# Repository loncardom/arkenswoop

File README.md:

# Arkenswoop

A WIP fork of [jimmerricks's Swoop](https://github.com/jimmerricks/swoop), which is a fork of [David Barr's Sweep](https://github.com/davidphilipbarr/Sweep), which is itself based on the fabulous [Ferris by Pierre Chevalier](https://github.com/pierrechevalier83/ferris).

| Front | Back |
| :---: | :---: |
|  |  |

### Features

⭕ Low profile Kailh Choc switches  
⭕ Hotswap  
⭕ Dual side-scrolling encoder  
⭕ Oled screens  
⭕ Power switch for battery management  
⭕ Bluetooth support w/ nice!nano  
⭕ Plate style case with mcu cover

### Components list

To build and use an Arkenswoop you will need:

* 1× PCB Kit (1.6mm thickness when ordering)
* 1× back plate kit (optional, 1.2mm thickness when ordering)
* 2× promicro compatible boards or 2 nice!nanos.
* 34× Kailh Choc v1 switches
* 34× Kailh Choc hotswap sockets (PG1350)
* 34× keycaps
* 34× SMD diodes (1N4148W, SOD-123)
* 2× side-scrolling encoders EVQWGD001
* 2× OLED LCD Display 128x32 SSD1306 (optional)
* 2× MCU cover (optional, 1mm thickness when ordering)
* 2× reset switches (optional; B3U-1000P(M))
* Some little rubber feet/bumpers (minimum of 4 on each side)
* 2× power switches (wireless only; MSK 12C02)
* 2× lipo batteries (wireless only; 301230 or 301228)
* 1× TRRS (not TRS!) cable (wired only)
* 2× TRRS Jack [PJ-320A] (wired only)
* 1× USB Cable (depends on your micro-controller choice)

## Images

<details>
    <summary>Assembled Arkenswoop 0.6.0</summary>
    
</details>
<details>
    <summary>Back of assembled Arkenswoop 0.6.0</summary>
    
</details>

# Altenswoop

An Arkenswoop inspired keyboard with a twist: the Z and / keys are moved to the side.

| Front | Back |
| :---: | :---: |
|  |  |

### Features

⭕ Low profile Kailh Choc switches  
⭕ Hotswap  
⭕ Dual side-scrolling encoder  
⭕ Oled screens  
⭕ Power switch for battery management  
⭕ Bluetooth support w/ nice!nano  
⭕ Plate style case with mcu cover

### Components list

To build and use an Altenswoop you will need:

* 1× PCB Kit (1.6mm thickness when ordering)
* 1× back plate kit (optional, 1.2mm thickness when ordering)
* 2× promicro compatible boards or 2 nice!nanos.
* 34× Kailh Choc v1 switches
* 34× Kailh Choc hotswap sockets (PG1350)
* 34× keycaps
* 34× SMD diodes (1N4148W, SOD-123)
* 2× side-scrolling encoders EVQWGD001
* 2× OLED LCD Display 128x32 SSD1306 (optional)
* 2× MCU cover (optional, 1mm thickness when ordering)
* 2× reset switches (optional; B3U-1000P(M))
* Some little rubber feet/bumpers (minimum of 4 on each side)
* 2× power switches (wireless only; MSK 12C02)
* 2× lipo batteries (wireless only; 301230 or 301228)
* 1× TRRS (not TRS!) cable (wired only)
* 2× TRRS Jack [PJ-320A] (wired only)
* 1× USB Cable (depends on your micro-controller choice)

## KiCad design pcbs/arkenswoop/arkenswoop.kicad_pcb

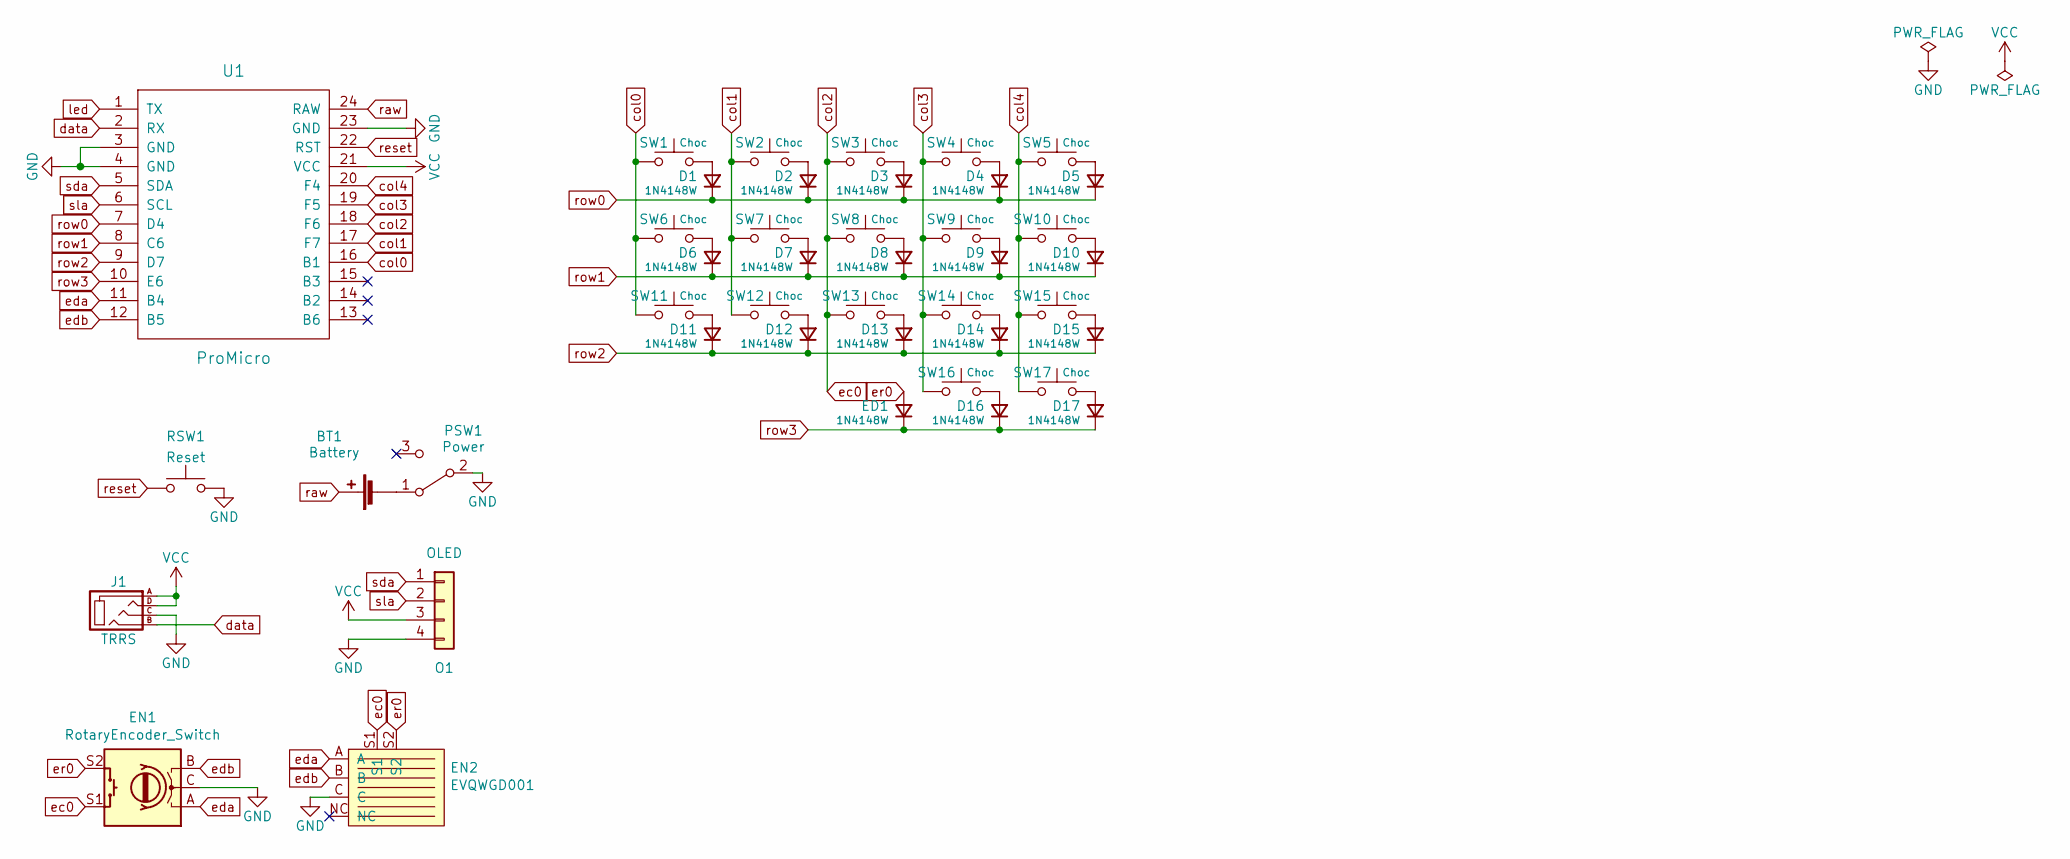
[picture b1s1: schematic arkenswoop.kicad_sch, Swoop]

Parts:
BT1: Battery; Battery_pads
D1, D2, D3, D4, D5, D6, D7, D8, D9, D10, D11, D12, D13, D14, D15, D16, D17: 1N4148W; D3_SMD
ED1: 1N4148W; D3_SMD
EN1: RotaryEncoder_Switch; RotaryEncoder
EN2: EVQWGD001; RollerEncoder
J1: TRRS; TRRS-3pin
O1: OLED; OLED_jumpers
PSW1: Power
RSW1: Reset
SW1, SW2, SW3, SW4, SW5, SW6, SW7, SW8, SW9, SW10, SW11, SW12, SW13, SW14, SW15, SW16, SW17: Choc
U1: ProMicro; ProMicro_jumpers

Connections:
GND: EN1.C, EN2.C, J1.C, O1.4, PSW1.2 (B), RSW1.2, U1.3 (GND), U1.4 (GND), U1.23 (GND)
unnamed: BT1.2 (-), PSW1.1 (A)
unnamed: D1.2 (A), SW1.2
unnamed: D2.2 (A), SW2.2
unnamed: D3.2 (A), SW3.2
unnamed: D4.2 (A), SW4.2
unnamed: D5.2 (A), SW5.2
unnamed: D6.2 (A), SW6.2
unnamed: D7.2 (A), SW7.2
unnamed: D8.2 (A), SW8.2
unnamed: D9.2 (A), SW9.2
unnamed: D10.2 (A), SW10.2
unnamed: D11.2 (A), SW11.2
unnamed: D12.2 (A), SW12.2
unnamed: D13.2 (A), SW13.2
unnamed: D14.2 (A), SW14.2
unnamed: D15.2 (A), SW15.2
unnamed: D16.2 (A), SW16.2
unnamed: D17.2 (A), SW17.2
VCC: J1.A, J1.D, O1.3, U1.21 (VCC)
col0: SW1.1, SW6.1, SW11.1, U1.16 (B1)
col1: SW2.1, SW7.1, SW12.1, U1.17 (F7)
col2: EN1.S1, EN2.S1, SW3.1, SW8.1, SW13.1, U1.18 (F6)
col3: SW4.1, SW9.1, SW14.1, SW16.1, U1.19 (F5)
col4: SW5.1, SW10.1, SW15.1, SW17.1, U1.20 (F4)
data: J1.B, U1.2 (RX)
eda: EN1.A, EN2.A, U1.11 (B4)
edb: EN1.B, EN2.B, U1.12 (B5)
er0: ED1.2 (A), EN1.S2, EN2.S2
led: U1.1 (TX)
raw: BT1.1 (+), U1.24 (RAW)
reset: RSW1.1, U1.22 (RST)
row0: D1.1 (K), D2.1 (K), D3.1 (K), D4.1 (K), D5.1 (K), U1.7 (D4)
row1: D6.1 (K), D7.1 (K), D8.1 (K), D9.1 (K), D10.1 (K), U1.8 (C6)
row2: D11.1 (K), D12.1 (K), D13.1 (K), D14.1 (K), D15.1 (K), U1.9 (D7)
row3: D16.1 (K), D17.1 (K), ED1.1 (K), U1.10 (E6)
sda: O1.1, U1.5 (SDA)
sla: O1.2, U1.6 (SCL)

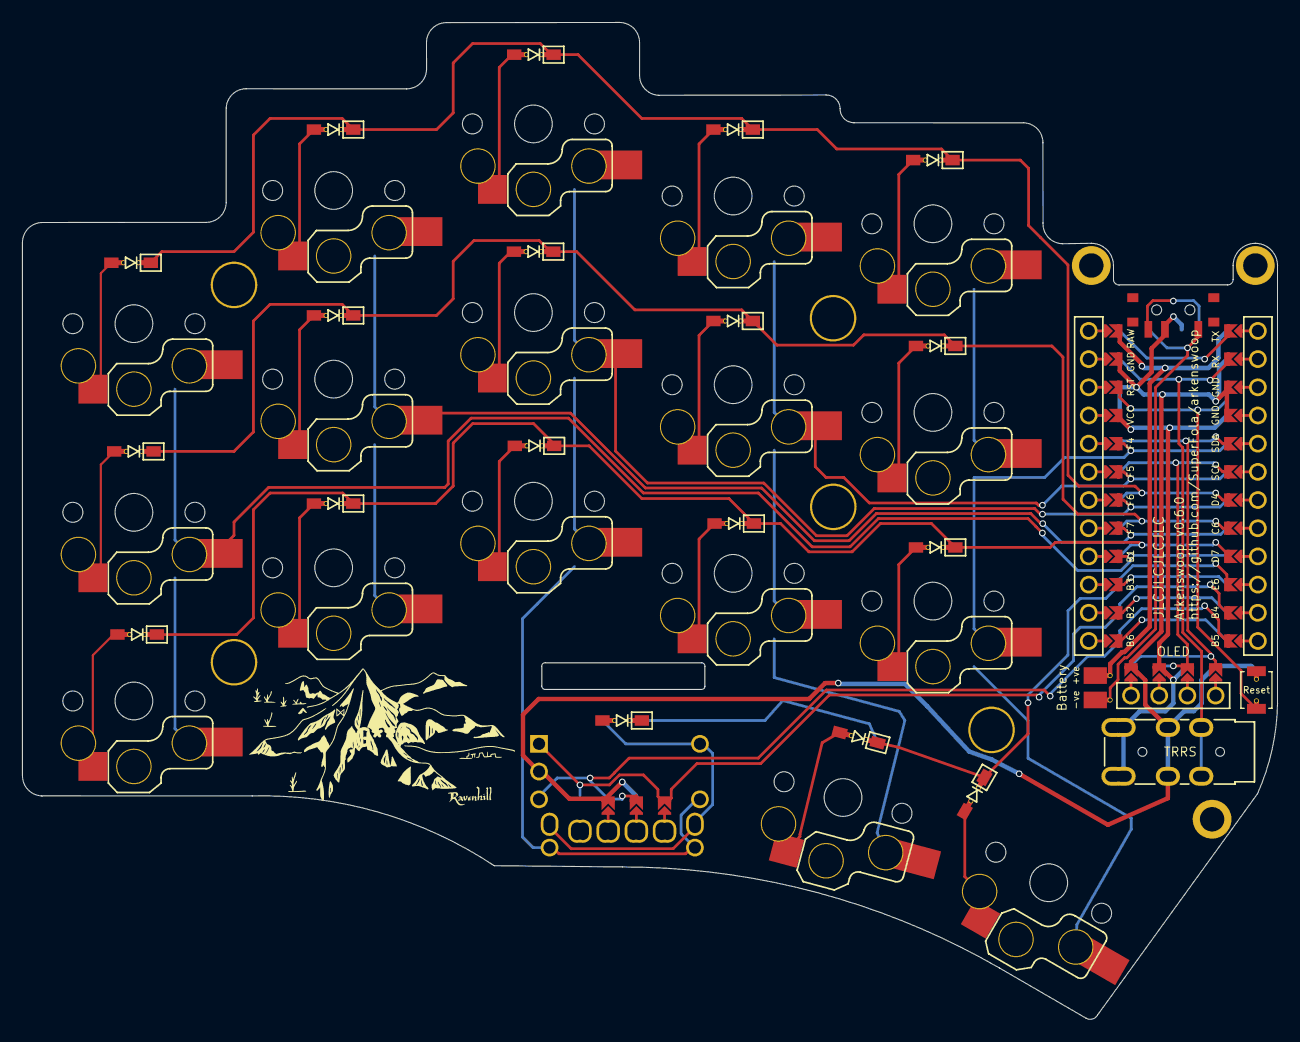
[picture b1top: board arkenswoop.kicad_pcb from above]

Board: 2 copper layers, 113.1 x 89.8 mm, 51 parts (0 on the bottom side), 36 nets.

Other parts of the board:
H1, H2, H3, H4, H4#2: M2 Hole; M2_hole_4.2mm
Ref**: Val**; M2_hole_3.5mm
Ref**#2, Ref**#3: Val**; M2_hole_3.5mm

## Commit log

2021-10-11 First commit of One Fell Swoop keyboard.
2021-11-14 Added files for the second version of the Swoop.
2021-11-28 Update Readme to warn against production
2021-11-28 v0.3: fixed route fail, changed shape, added cover
2021-11-28 Added plates for a v0.3 case.
2021-12-11 Footprints for the Swoop choc and mx
2021-12-11 Reorganised the Choc
2021-12-11 Added the Swoop MX
2021-12-11 Removed backups.
2021-12-11 Name change
2022-02-02 Repository reorganised.
2022-02-02 Plates and gerbers removed.
2022-02-02 Files renamed and corrections made.
2022-02-03 Tidied up the library.
2022-02-03 Fixed the cover
2022-02-03 New images.
2022-08-05 Removed LED strip and normalised LED order.
2022-09-01 Add preview build workflow
2022-09-01 Add upload artifacts
2022-09-01 Add export folders
2022-09-01 Update docs
2022-09-02 Add howarya to header
2022-09-02 Add oled display in component list
2022-09-02 Update component list
2022-09-03 Add .gitignore & Remove ignored files
2023-05-28 Adding the arkenswoop as a remix of the Swoop 0.4.2
2023-05-28 Clean up, see original files on the parent repo
2023-06-09 adding build guide
2023-06-09 starting to work on the firmware to support vial
2023-06-09 wip: vial integrations and liatris leds
2023-06-09 small update to readme and plates
2023-06-11 updating firmware
2023-06-11 working on the liatris rgb
2023-06-11 adding build images
2023-06-12 moving the encoder about 0.3mm down ; this should give enough clearance to the nearest key and its keycap
2023-06-12 enabling unicode in the firmware
2023-06-12 removed leds footprint
2023-06-12 removed leds from schematic
2023-06-12 added silkscreens and exported 3D renders of the modified pcb and plates
2023-06-12 removed leds from the readme
2023-06-12 changed the holes for 2.2mm on the back plates
2023-06-12 customized pcb to have the jlcpcb order number under the mcu
2023-06-25 adding hotswap arkenswoop
2023-06-25 redoing the plates because of the larger size of the hotswap version
2023-06-25 removing old soldered version
2023-06-25 adding images of the back plates
2023-06-25 added silk on pcb
2023-06-25 added renders of pcbs
2023-06-25 adding gerbers
2023-06-25 added switch plate
2023-07-01 firmware: updating the layout with kle to match the disposition of the keyboard
2023-07-02 fixing the weird macros behavior (closes #1)
2023-07-09 moved the standard Arkenswoop to pcbs/3x5_2
2023-07-09 adding the altenswoop, an arkenswoop with a north-west pinky cluster
2023-07-09 moving the qmk firmware to firmware/qmk/ to make room for kmk firmware
2023-07-23 more layers are always better
2023-07-28 redoing the switch plates cutouts and adding a proper kicad library
2023-07-28 updating kailh reversible footprint to add switch outline
2023-07-28 adding the net classes to the sockets which got removed when updating footprints
2023-07-28 updating readme todolist
2023-07-30 adding new images
2023-08-10 adding the altenswoop
2023-08-10 fixing traces thanks to DRC on the altenswoop
2023-08-10 updating readme to add altenswoop
2023-08-23 adding mcu cover
2023-08-23 removing gerbers/ folders, only keeping gerbers.zip
2023-08-23 updating qmk firmware since vial updated
2023-08-23 updating readme, no more todos!
2024-08-08 feat(qmk): adding caps word support
2024-12-11 fixes for leonardo
2024-12-29 Update components list to add the forgotten diodes
